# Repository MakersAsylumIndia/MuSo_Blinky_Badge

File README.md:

# MuSo Blinky Badge
a really easy, learn to solder Museum of Solutions + Maker's Asylum Badge

**forked from Maker's Asylum Project #4 MAP4**

***FEATURES***

1. Two LED's with series current limit resistors
2. One CR2032 Coin Battery
3. Use RGB LEDs, or all White LEDs or whatever you choose
5. Use a Blinking LED
6. Replace Resistor with LDR to have light controlled brightness

***LEARN***

1. How to Solder
2. Resistor Color Code
3. Use of Multimeter to check LED, Resistor and Battery

DISCUSSION FORUM : TBD

rev1 renders

License
-------
[CERN Open Hardware Licence v1.2 ]

[CERN Open Hardware Licence v1.2 ]:http://www.ohwr.org/attachments/2388/cern_ohl_v_1_2.txt

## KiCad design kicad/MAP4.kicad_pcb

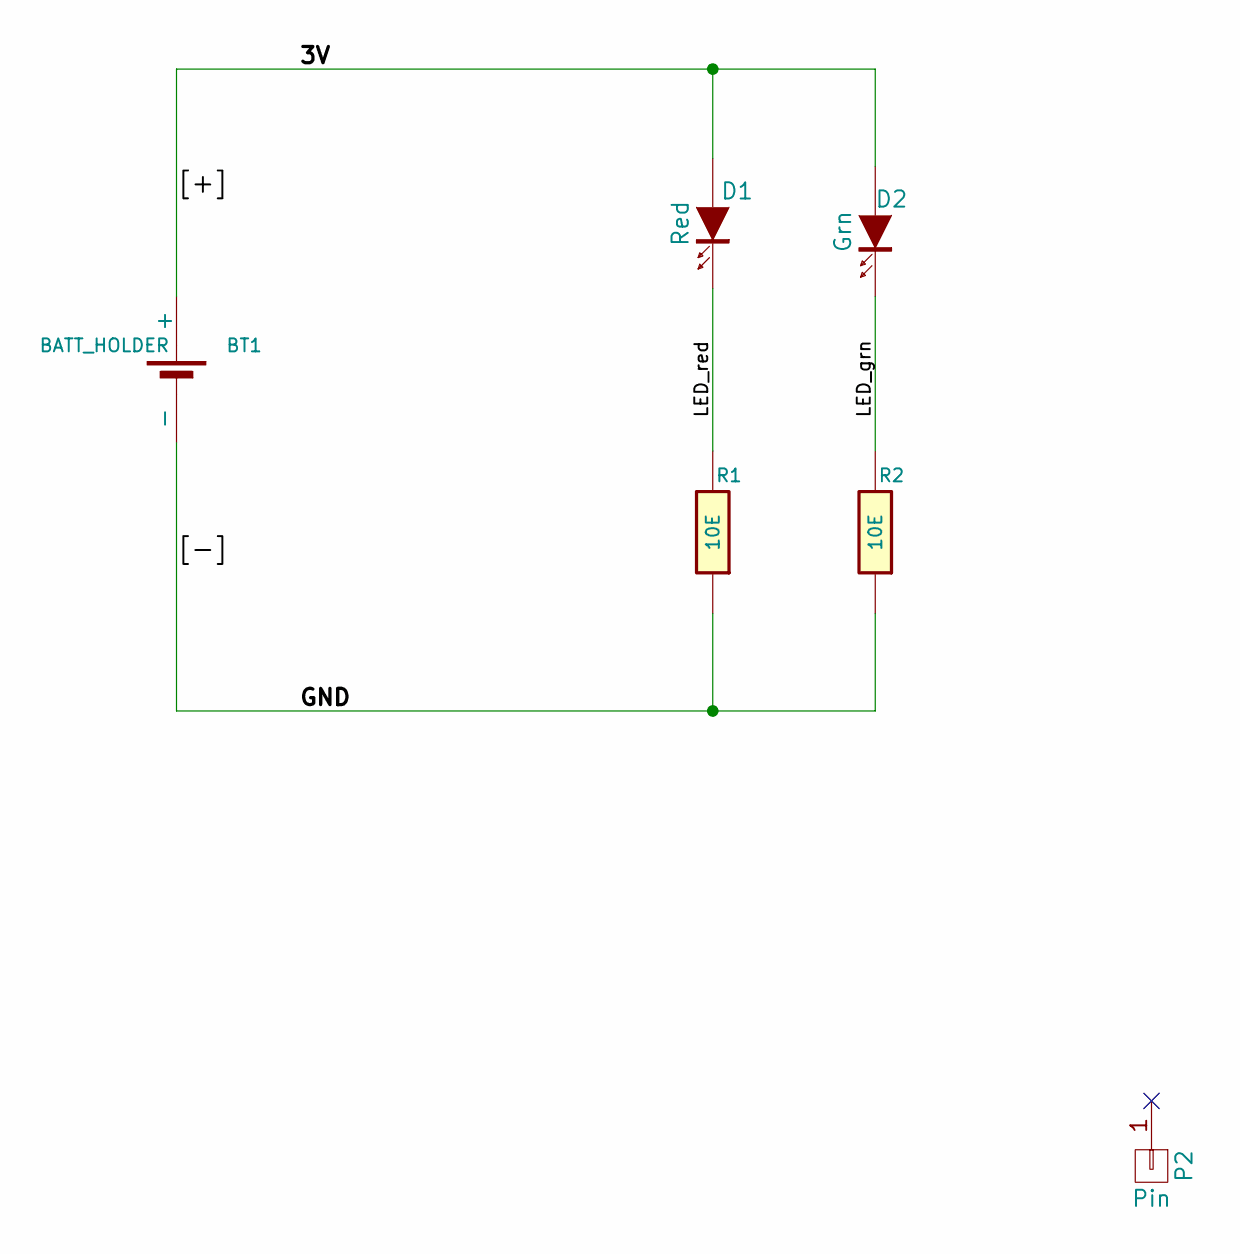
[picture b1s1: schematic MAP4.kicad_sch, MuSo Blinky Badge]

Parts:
BT1: BATT_HOLDER; cr2032_02
D1: Red; LED-5MM
D2: Grn; LED-5MM
P2: Pin; MTG_12x3_slot
R1, R2: 10E; r_0805

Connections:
/3V: BT1.1 (+), D1.1 (A), D2.1 (A)
/GND: BT1.2 (-), R1.1, R2.1
/LED_grn: D2.2 (K), R2.2
/LED_red: D1.2 (K), R1.2

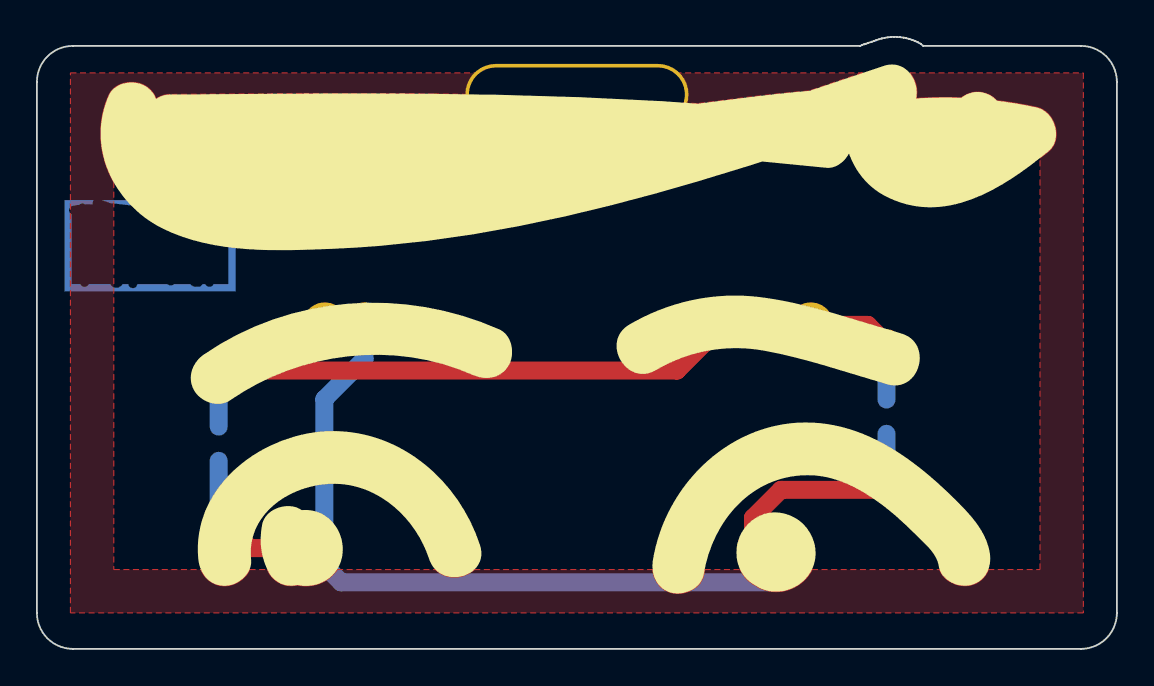
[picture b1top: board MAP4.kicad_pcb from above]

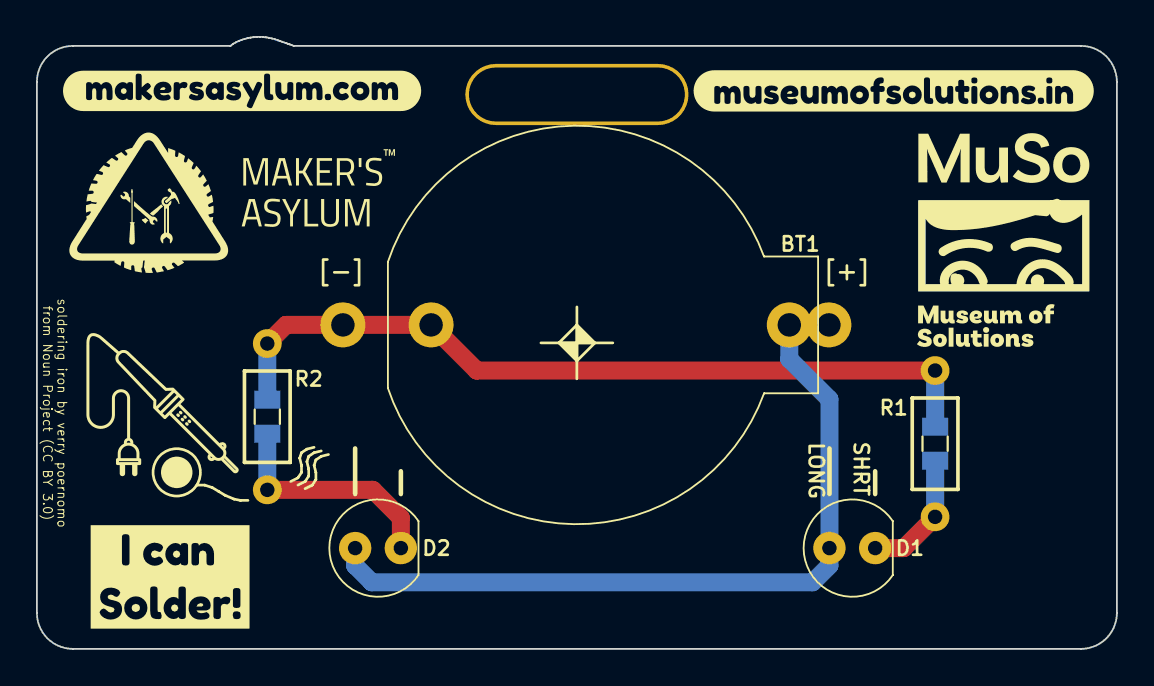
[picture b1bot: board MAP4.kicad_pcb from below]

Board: 2 copper layers, 60.0 x 34.0 mm, 9 parts (6 on the bottom side), 4 nets.

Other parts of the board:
kibuzzard-6554D52C: G***; kibuzzard-6554D52C
kibuzzard-6554D613: G***; kibuzzard-6554D613
kibuzzard-655707C1: G***; kibuzzard-655707C1

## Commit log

2023-12-02 added assembly images

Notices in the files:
kicad/MAP4.kicad_pcb:
from Noun Project (CC BY 3.0)
